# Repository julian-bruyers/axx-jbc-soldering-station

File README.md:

## Personal fork of Axel Johansson's AxxSolder
> [!NOTE]
> The purpose of this fork is not to continue the development of the offical [AxxSolder](https://github.com/AxxAxx/AxxSolder)
> but rather for some personal graphical and functional changes for my own taste. If you stumbled upon this and are interested
> in the AxxSolder project, please check out the original repository and [shop](https://www.5dimensions.se/) of Axel Johansson
> to support the project. All credits belong to him and the open-source contributers of the original project.

## AxxSolder Overview
AxxSolder is a STM32 based soldering iron controller for JBC C115, C210 and C245 style cartridges.
Two different versions are designed around the same PCB and software - one soldering station based on the [JBC ADS stand](https://www.jbctools.com/ad-sf-stand-for-t210-t245-handles-product-2018.html) and one portable version. The AxxSolder hardware takes a DC input source of 9-24V OR a USB-C Power Delivery source. The recommended power supply is a Meanwell [LRS-150-24](#recommended-power-supply) which can power all compatible JBC irons at full power. If a 65W, 20V USB-PD supply is used then NT115 and T210 handles can be powered at full power and T245 at limited power. The power limiting is automatic and AxxSolder reads the power capability of the USB-PD source during the negotiating phase and reduces the output power accordingly.
The software is written for the [STM32G431CBT6](https://www.st.com/en/microcontrollers-microprocessors/stm32g431cb.html) and implements a PID controller for temperature regulation, TFT display driver, sleep functions for when the handle is at rest and various user settings to name a few.
Enclosures for both station and portable versions are 3D printed and design files are available under [/CAD](https://github.com/AxxAxx/AxxSolder/tree/main/CAD). A video showing the AxxSolder station can be found under [DEMO](#demo). A *bill of materials* (BOM) with individual component prices can be found under [/bom](https://github.com/AxxAxx/AxxSolder/tree/main/AxxSolder_hardware/bom).

## Table of Contents
- [AxxSolder Overview](#axxsolder-overview)
- [Questions and support](#questions-and-support)
- [Features](#features)
- [DEMO](#demo)
- [Schematic](#schematic)
- [PCB](#pcb)
- [AxxSolder Station](#axxsolder-station)
- [AxxSolder Portable](#axxsolder-portable)
- [Recommended power supply for tip grounding](#recommended-power-supply-for-tip-grounding)
- [Handle identification and connections](#handle-identification-and-connections)
- [Firmware update](#firmware-update)
- [First start up after build](#first-start-up-after-build)
- [Settings](#settings)
- [PID control](#pid-control)
- [Cartridge differences](#cartridge-differences)
- [Temperature calibration](#temperature-calibration)
- [Temperature measurement](#temperature-measurement)
- [Current measurement](#current-measurement)
- [Disclaimer](#disclaimer)

## Features
- The tip temperature is set by a rotary encoder. Pressing the encoder puts AxxSolder into Sleep mode and heating is turned off, press again to wake up.
- AxxSolder is capable of driving C115, C210 and C245 style cartridges from JBC. With two handle sense inputs AxxSolder can determine if the connected handle is either a NT115, T210 or T245 and adjust max output power accordingly. The max output power is software limited to 130 W for T245, 65 W for T210 and 22 W for NT115 handles.
- When the handle is put into the stand (connected to Stand_sense) AxxSolder goes into "Standby mode". On the portable version an aluminium plate is mounted in the case and allows the AxxSolder to go into Standby mode when the cartridge or handle rests against it. After 10 min in Standby mode AxxSolder goes into "Sleep mode" and heating is completely turned off. This is similar to what JBC calls [Sleep and Hibernation](https://www.jbctools.com/intelligent-heat-management.html).
- If AxxSolder is left in normal running mode for longer than 30 min, the station automatically goes into sleep mode after 30 min as a safety feature.
- Should the temperature ever go higher than 480 deg C overheating is detected and the station goes into sleep mode in order to protect the tip.
- At start-up any USB-PD source is detected and the highest possible power is negotiated. AxxSolder limits the soldering iron output power to the max output power of the USB-PD source automatically. The maximum power output is displayed at the top of the power bar graph on the display.
- User settings are stored in non-volatile flash and can be configured via a settings menu described in [SETTINGS](#settings).
- The two buttons are used to store temperature presets, e.g. 330 deg C and 430 deg C. Both preset temperatures are configurable in the settings menu. The stored preset temperature can be updated to the current set temperature by long-pressing the preset button.
- There is a 3.3 V logic level output (GPIO4) that can be configured to go high when the iron is in Run mode, controlling e.g. fume extractor via a MosFET or relay.
- The TFT display used in this project is a 2 inch 320x240 Color TFT display [2.0" 320x240 Color IPS TFT Display](https://www.adafruit.com/product/4311) and shows information about:
  - Set temperature
  - Actual temperature
  - Current power as a bar graph
  - In case of sleep mode, the power bar shows "ZzZzZz"
  - In case of Standby mode, the power bar shows "STANDBY"
  - Input voltage
  - MCU temperature
  - Current detected handle type
  - Current max power output
  - Current power source USB-PD / DC

## Schematic
The schematic for AxxSolder is shown below. Both station and portable versions use the same PCB and software. The MCU is a [STM32G431CBT6](https://www.st.com/en/microcontrollers-microprocessors/stm32g431cb.html).

## PCB
The PCBs are designed in KiCad and manufactured by [PCBWay](https://www.pcbway.com/). PCBWay has sponsored this project with PCBs and stencils. The support and quality from PCBWay is great and therefore PCBWay is the recommender PCB supplier for this project. As some components have a rather fine pitch (0,5 mm as of the LQFP-48 package of the STM32) and some packages are "no lead" with a bottom thermal pad e.g. the WSON-8 package of the OPA2387 it is recommended to use a stencil to apply solder paste and then reflow the board using either a reflow oven or hot-plate. The boards on the image below were reflowed on a hot-plate (a homemade AxxPlate). A microscope is also recommended and helpful during assembly.
Printed Circuit Boards with assembled components are shown in the image below.

A 3D view (from and back) of the AxxSolder PCB is generated with KiCad and shown below.

## AxxSolder Station
The preferred setup is to pair AxxSolder with the [JBC ADS stand](https://www.jbctools.com/ad-sf-stand-for-t210-t245-handles-product-2018.html). This makes a very nice, compact and powerful soldering station. The JBC ADS stand is paired with a custom 3D printed enclosure for AxxSolder and the PCB is mounted with two mounting brackets. All 3D printed parts are available under [/CAD](https://github.com/AxxAxx/AxxSolder/tree/main/CAD).

The JBC ADS stand comes with a silicone cable fitted with two Binder 99-0621-00-07 connectors. In order to use this cable a Binder 99-0624-00-07 is mounted into the AxxSolder enclosure and wired as the image below:

By default, the stand separates the two signals coming from the "tool rest position" and the "tip change position" and does NOT have two separate connections for tip sensing 1 and 2 as is needed if NT115, T210 and T245 handles should all be automatically detected. Therefore, a modification is done to the PCB inside the JBC ADS stand in order to combine the "tool rest position" and the "tip change position" sense into one connection and separate the two tip sense connections. This is shown in the image above. The stand is held together with two PH0 screws from the side.
NOTE: This modification of the stand is only needed if you want to be able to use NT115, T210 and T245 with your JBC ADS stand. If you know that you will only be using T210 and/or T245 you can change the user setting: Detect NT115 to "NO" in the settings in order for T210 and T245 to be automatically detected with a un-modified JBC ADS stand.

The JBC ADS stand is an expensive piece and thankfully there are many alternatives online for the one who wants to save some money. The community on the AxxSolder Discord channel has created many enclosures for alternative stands such as the GEEBOON SDC02, and some of the AiXun stands. Some of the models are availible under [Alternative stands](https://github.com/AxxAxx/AxxSolder/tree/main/CAD/Alternative_enclosures_and_designs) .

## AxxSolder Portable
It is often nice to have a compact and portable soldering iron controller for when you are away from your comfortable desk. A neat powerful package with the same capabilities as your main soldering station. This is why AxxSolder Portable was designed. The only difference between AxxSolder station and Portable is the enclosure.
As AxxSolder accepts an input of 9-24 V it is compatible with a range of battery options. The author usually use a battery pack consisting of 12 Samsung INR18650 35E in a 3S4P configuration which works very well.
The portable version has an aluminium tab on the enclosure connected to the same input on the PCB as the "handle rest" on the station version. This allows the user to rest the iron onto the aluminium tab and automatically enter sleep mode.

The connections from the handle to the PCB through the Hirose RPC1-12RB-6P(71) connector is shown below. The Stand_sense in the portable version is connected to the aluminium plate which tells the AxxSolder to go into sleep mode when in contact with the soldering iron.

## Recommended power supply for tip grounding
In order to be able to ground the tip of the soldering iron the user MUST use a power supply with a floating output (SELV) and connect protective earth to the ground terminal on AxxSolder. No other devices should share this DC power other than AxxSolder itself. A well-suited power supply with floating output (SELV) is the Meanwell LRS-150-24. It is rated for 156 W at 24 V. By using this kind of power supply, AxxSolder can be connected directly its DC output and to mains earth thus keeping the tip of the soldering iron at earth ground potential. There is a 1A fuse after the earth terminal in paralell with a 1M resistor on the AxxSolder.
A printable cover protecting the terminals of the for LRS-150-24 can be found under [/CAD](https://github.com/AxxAxx/AxxSolder/tree/main/CAD).

Another suitable power supply is the Meanwell XLG-150-24 which has a slightly different form factor and is fully enclosed.

## Handle identification and connections
In order for AxxSolder to know which type of handle (NT115, T210, T245) is attached specific pins inside the handle connector must be connected (bridged with a jumper wire). By default, the original JBC handle T245 has NO bridged pins while inside the connector of the original JBC T210 the pins 5 and 6 are bridged with a jumper wire. The original NT115 handle from JBC has a different connector and must be modified accordingly. All the necessary connections are shown in the image below.
When powering on AxxSolder for the first time after doing these connections inside the handle connector it is wise to attach a handle without its cartridge and ensure that AxxSolder detects and shows the correct handle type on the display.
Failing to detect the handle type may cause permanent damage to the cartridge as the temperature calibration and max allowed power will be wrong.
❗WARNING❗ It has been discovered that some JBC clones have different pins bridged by the manufacturer. For example: Some AiXun T210 handles have pin 1 and 6 bridged, instead of pin 5 and 6 as AxxSolder requires for T210 handles. It is however easy to open up the connector and do the required pin connection.

## Firmware update
Flashing or updating the firmware on the STM32 MCU can be done in two ways, by using a SWD programmer or directly via USB.

### SWD programmer
These come in a variety of models and are available from several different places online. In the below example a [STLINK-V3MINIE](https://www.st.com/en/development-tools/stlink-v3minie.html) SWD programmer is used. The MCU is programmed by the following steps:
1. Disconnect any soldering iron handles from AxxSolder during the firmware update process.
2. Download the latest AxxSolder.bin file from [Releases](https://github.com/AxxAxx/AxxSolder/releases)
3. Connect your SWD programmer to the target MCU with GND, 3.3V, (N)RST, SWCLK, SWDIO
4. If your SWD programmer *can not* supply 3.3V it is necessary to power the AxxSolder from an external supply.
5. Start your programming software. [STM32CubeProgrammer](https://www.st.com/en/development-tools/stm32cubeprog.html) is used in this example.
6. Connect to the target by selecting *ST-LINK* and click on *Connect*
7. Load the latest AxxSolder.bin downloaded in *Step 2* by clicking *Open file* and select the downloaded binary file.
8. Write the firmware to the MCU by clicking *Download*.
9. If you get the message *File download complete* everything succeeded and the SWD programmer can be disconnected and AxxSolder power cycled once and AxxSolder should boot.

### USB (DFU mode)
1. Disconnect any soldering iron handles from AxxSolder during the firmware update process.
2. Download the latest AxxSolder.bin file from [Releases](https://github.com/AxxAxx/AxxSolder/releases)
3. Connect AxxSolder via USB to a computer that runs [STM32CubeProgrammer](https://www.st.com/en/development-tools/stm32cubeprog.html).
4. Hold down the most right button while powering on AxxSolder to enter DFU mode.
5. Connect to the target by selecting *USB* and click on *Connect*
6. Load the latest AxxSolder.bin downloaded in *Step 2* by clicking *Open file* and select the downloaded binary file.
7. Write the firmware to the MCU by clicking *Download*.
8. If you get the message *File download complete* everything succeeded and the USB cable can be disconnected.
9. Power cycle once and AxxSolder should boot.

## First start up after build
The first start up after you have built your AxxSolder can be intense. Double check all solder connections under a loupe/microscope. Especially the OPA2387, LTC4440 and the STM32G431 are small packages with tight pad spacing and can have solder bridges. Do also double check the connections to the soldering iron/stand which are shown in this document under [AxxSolder Station](#axxsolder-station) and [AxxSolder Portable](#axxsolder-portable).
The first thing to do after you have double-checked everything is to follow the steps under [Firmware update](#firmware-update). It is wise to do the first programming of AxxSolder without any handle piece and with only 3.3 V, not VDD. After the programming is done you can now power up AxxSolder again via either with 3.3 V, this time you can attach your handle. This allows you to test that your handle type is detected correctly (the detected handle type NT115/T210/T245 is shown in the display). The Standby feature can also be tested by touching the stand (STAND Input).
If the handle is detected correctly, the Standby function works and the display works you proceed to test the 7.35V DC/DC. This is done by once again disconnect the handle, but this time apply current limited 9-24 V VDD. 100 mA at 24 V is enough to check that the display starts and that you can measure the 3 bus voltages; 3.3V, 7.35V and VDD. If the bus voltages look good and the display shows the main screen you are ready to apply full VDD power and attach the soldering handle.
If you are not 110% sure about your soldering/connections it is wise to be on the safe side and keep your soldering tip in a water bath in over to prevent it from over-heating in an uncontrolled manner. During the development this method was used and saved a few of those expensive JBC cartridges..

## Settings
To access the user settings the user holds down the encoder button at start-up or long-press the encoder button. A SETTINGS text is then presented and the button can be released. While in the settings there are several parameters available.
| Setting | Description  | Unit | Default |
|---------|------|----------------------|----------------------|
|Startup Temp °C|Default temperature selected after boot|deg C|330|
|Temp Offset °C|Temperature offset applied to measured temperature|deg C|0|
|Standby Temp °C|Temperature to go to after handle is set in stand|deg C|150|
|Standby Time [min]|Time for which standby temperature is held before cooling down|minutes|10|
|Sleep Time [min]|Time that the iron can be ON before cooling down (safety feature)|minutes|30|
|Buzzer Enable|Enable or Disable the buzzer|YES/NO|YES|
|Preset Temp 1 °C|Preset temperature for button 1|deg C|330|
|Preset Temp 2 °C|Preset temperature for button 2|deg C|430|
|GPIO4 ON at run|Enable 3.3V output on GPIO4 when the iron is in run mode|YES/NO|NO|
|Screen rotation|Rotate the screen|0 deg, 90 deg, 180 deg, 270 deg|0 deg|
|Limit Power [W]|Limit the output power|"0"=no user limit, "5"=5 W, "10"= 10 W, "15"= 15 W ...|0|
|I measurement|Measure the heater current|YES/NO|YES|
|Startup beep|Beep after startup|YES/NO|YES|
|Temp in celcius|Show temperatures in Celcius and not Fahrenheit|YES/NO|YES|
|Temp cal 100 °C|Actual temperature at 100 °C|deg C|100|
|Temp cal 200 °C|Actual temperature at 200 °C|deg C|200|
|Temp cal 300 °C|Actual temperature at 300 °C|deg C|300|
|Temp cal 350 °C|Actual temperature at 350 °C|deg C|350|
|Temp cal 400 °C|Actual temperature at 400 °C|deg C|400|
|Temp cal 450 °C|Actual temperature at 450 °C|deg C|450|
|Serial DEBUG|Print debug over serial|YES/NO|NO|
|Displayed temp filter|Moving average filter length|Lenght|5|
|Startup temp is previous temp|Startup temp is previous used temp|YES/NO|NO|
|3-button mode|Use 3-button mode|YES/NOF|NO|
|Beep at set temp|Beep at set temp|YES/NO|YES|
|Beep tone|Beep tone|0,1,2,3|0|
|Momentary stand|Use the stand as momentary switch to go between modes (useful on AxxSolder Portable)|YES/NO|NO|
|Show power|Current power under the bar graph is displayed in this unit|W/%|W|
|Detect NT115|Detect NT115 handles or not. Useful to turn OFF for un-modified JBC SDA stands|YES/NO|YES|
|-Load Default-|Load default parameters|N/A|N/A|
|-Save and Reboot-|Exit and Save|N/A|N/A|
|-Exit no Save-|Exit without Save|N/A|N/A|

## PID control
The thermal mass and heat convection differs between different tip designs. Therefore the PID parameters should in theory be adjusted to each different cartridge. As a matter of simplification, the PID parameters are only different between the different handle types, NT115, T210 and T245. This gives a good thermal performance in conducted tests.
```c
/* Cartridge type specific PID parameters */
#define KP_NT115        5
#define KI_NT115        2
#define KD_NT115        0.3
#define MAX_I_NT115     300

#define KP_T210         7
#define KI_T210         4
#define KD_T210         0.3
#define MAX_I_T210      300

#define KP_T245         8
#define KI_T245         2
#define KD_T245         0.5
#define MAX_I_T245      300

/* General PID parameters */
#define PID_MAX_OUTPUT          500
#define PID_UPDATE_INTERVAL     25
#define PID_ADD_I_MIN_ERROR     75
double PID_NEG_ERROR_I_MULT =   7;
double PID_NEG_ERROR_I_BIAS =   1;

/* Max allowed power per handle type */
#define NT115_MAX_POWER         22
#define T210_MAX_POWER 	        65
#define T245_MAX_POWER 	        130
```
The PID parameters are adjusted to achieve a fast response with minimum overshoot and oscillation. The below image is showing the set temperature, actual temperature response as well as the P, I and D contributions during a heat-up cycle from 25 deg C to 330 deg C. This heat-up sequence takes ~1.5 seconds for a C210-007 cartridge.

## Cartridge differences
Cartridges from JBC do all contain a thermocouple element to read the tip temperature and a resistive heater element. The configuration of thermocouple and heater element differ slightly between cartridge models. In order to determine the internal configuration of the cartridges two cross sections were done. These show clearly how the C210 and C245 cartridges are constructed internally. The images can be seen here: [https://www.eevblog.com/forum/projects/axxsolder-jbc-soldering-controller](https://www.eevblog.com/forum/projects/axxsolder-jbc-soldering-controller/msg5124267/#msg5124267).
As the thermocouple output also differs (see my measurements [Temperature calibration](#temperature-calibration)) the correct handle/cartridge type has to be set. This is done automatically be the inputs "Handle_sense_1" and "Handle_sense_2" This can be done thanks to the design of the handle connector. For the JCB T210 handle pin 5 and 6 are connected internally in the connector and for NT115 pin 3 and 5 should be connected. This allows AxxSolder to sense which handle is connected and assign correct thermocouple correction, PID parameters and max output power.

## Temperature calibration
The voltage from the thermocouple embedded inside the cartridge is amplified by an OPA2387 operational amplifier and then read by the ADC of the MCU. To correlate the measured ADC value to the cartridge temperature experiments were done. A constant power was applied to the heating element of the cartridge and the ADC value was read as well as the actual tip temperature. The tip temperature was measured by a "Soldering Tip Thermocouple" used in e.g. the Hakko FG-100.
The measured data was recorded and plotted for both the C115, C210 and C245 cartridges. The specific cartridges used were the C115112, C210-007 and C245-945. The measured data were fitted to polynomial equations:
$Temp_{C115}[deg] =  5.10e^{-5} * ADC^2 + 0.42* ADC + 20.15$
$Temp_{C210}[deg] =  4.22e^{-6} * ADC^2 + 0.32* ADC + 20.97$
$Temp_{C245}[deg] = -4.73e^{-7} * ADC^2 + 0.12* ADC + 23.78$
These are then used in the software to retrieve correct tip temperatures.

The user can adjust the temperature calibration at 6 points in order to compensate for variations in the cartridge thermocouple.
To calibrate temperature(s):
- Make sure that the temperature calibration values are at their default nominal values in the settings.
- Set AxxSolder to the temperature that you want to calibrate. for example 300 deg C.
- When AxxSolder stabilizes around the setpoint, measure the actual tip temperature by using a soldering tip thermocouple, for example the HAKKO FG-100B.
- Input the actual measured temperature, let's say 302 deg C into the 300 deg C calibration setting ("Temp cal 300" = 302).

AxxSolder will then use this calibration point and correct the temperature accordingly. It will do so linearly between all calibration points.

## Temperature measurement
As the thermocouple and heater element is connected in series inside the JBC cartridges and the thermocouple voltage measures over the same pins as the heating element we have to be careful when to do the temperature measurement. In order to not disturb the thermocouple measurement with heater element switching, the switching is turned off for 0.5 ms just before the temperature measurement is taken. The 0.5 ms delay ensures that the switching is turned off and the thermocouple signal is stabilized around a stable voltage.
The measured signal over the thermocouple is clamped to 3.3V with a BAV199 Schottky diode in order to protect the op-amp OPA2387. The voltage measurement is taken by the internal ADC in DMA mode with a circular buffer. The buffer holds several measurements which are averaged and filtered in software.
The yellow curve in the image below (Channel 1) shows the PWM signal driving the gate of the MOSFET.
The green curve shows the amplified voltage between GREEN and RED wire in the JBC handle for at 330 degree C and 5% power and the purple 25 degree C and at 80% power (the tip held under water trying to heat up).
The blue pulse indicates the wait time of 0.5 ms and the purple pulse is where the ADC is sampled.

## Current measurement
The current is sampled four times per second by a 30 us current pulse through the heater. This is done both to check if there is a functioning tip in the handle (otherwise the display shows "---" at current temp) and to be able to calculate the power drawn by the heater. By knowing how much the heater draws in ampere the actual power can be calculated by knowing the bus voltage and pulse duty cycle. to measure the current the gate to the MOSFET is turned on, 10 us later the voltage over the current shunt is sampled by the ADC and the result is converted. This is shown the image below.

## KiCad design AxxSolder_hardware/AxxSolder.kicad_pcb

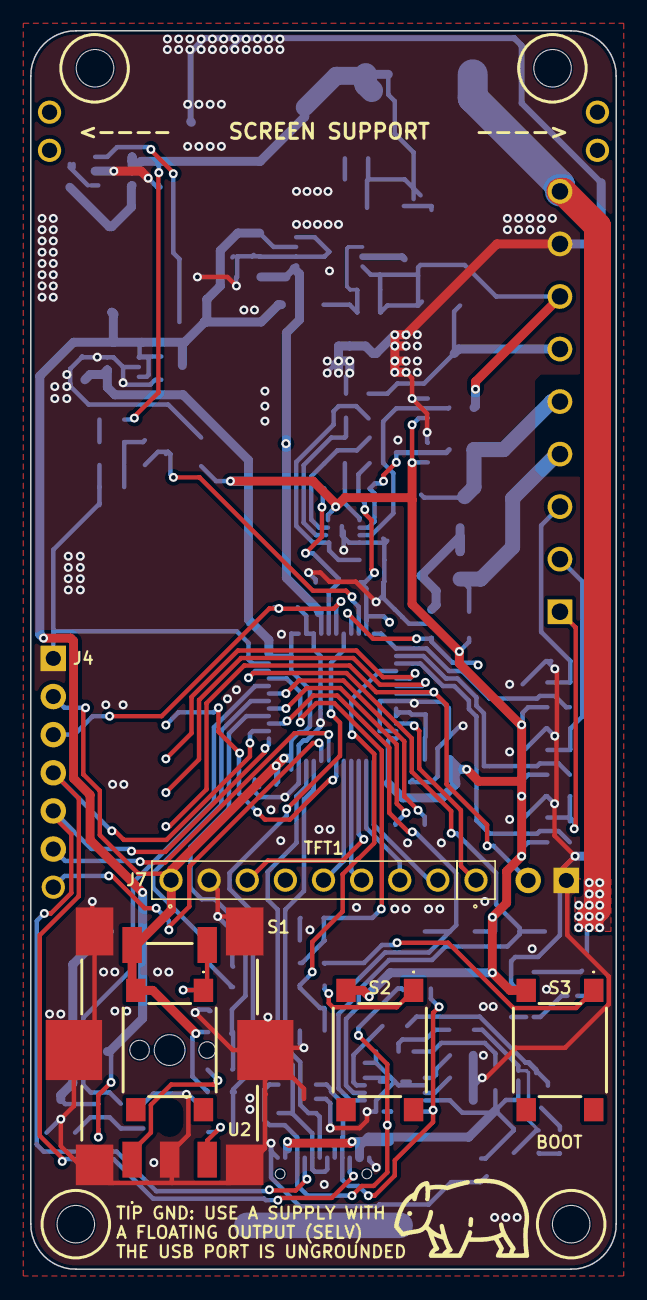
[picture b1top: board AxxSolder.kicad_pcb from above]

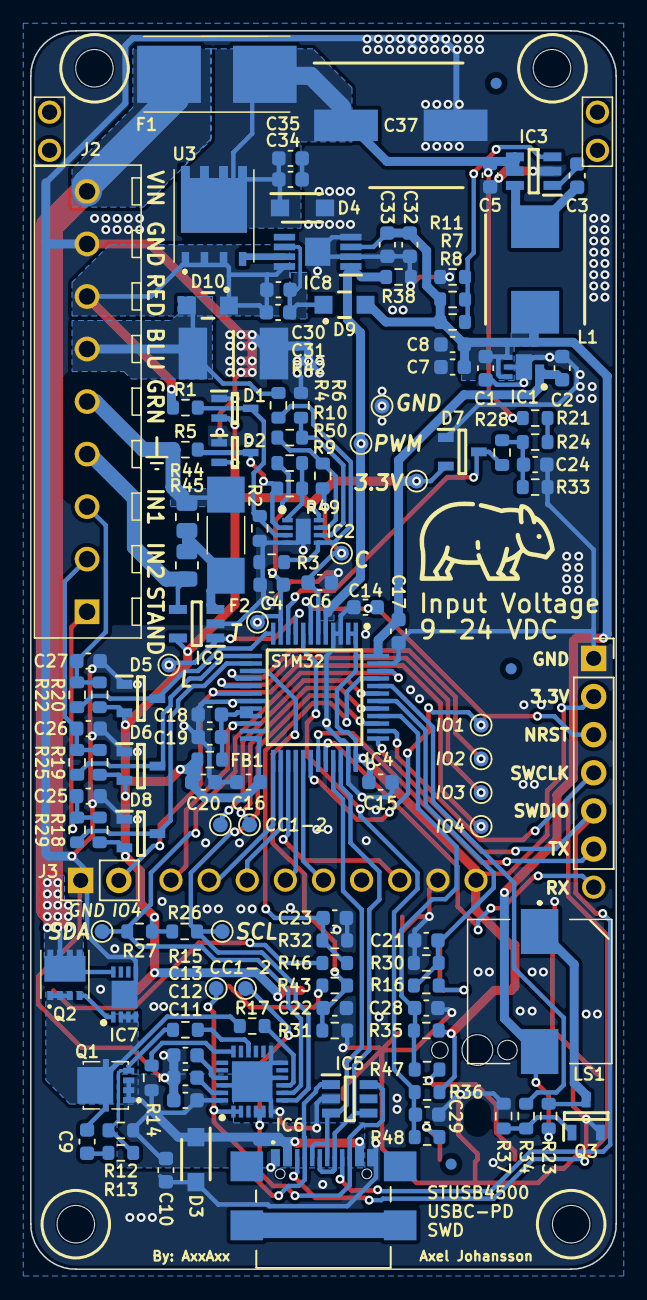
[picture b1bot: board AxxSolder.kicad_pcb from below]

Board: 2 copper layers, 39.0 x 82.5 mm, 148 parts (134 on the bottom side), 81 nets.

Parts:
C1, C2, C5, C7, C8, C10, C11, C12, C13, C19, C20, C30, C31, C32, C34, C35: 10u; C_0603_1608Metric
C3, C9, C14, C15, C16, C17, C18, C21, C22, C23, C24, C25, C26, C27, C28, C29, C33: 100n; C_0603_1608Metric
C4, C6: 1n; C_0603_1608Metric
C37: 220u; CAPAE830X1050N
D1, D2: BAV199WQ-7; SOT65P210X110-3N
D3, D4: SMF4L24AT1G; SODFL3619X98N
D5, D6, D7, D8: BAT54S; SOT95P230X110-3N
D9, D10: PMEG6020ER; PMEG6020ER115
F1: 0154007.DR; 0154100DR
F2: SF-2410FP100W-2; SF2410FP100W2
FB1: BLM18HE601SN1D; R_0603_1608Metric
FID1, FID2, FID3: Fiducial; Fiducial_0.75mm_Mask1.5mm
H1, H2: MountingHole; MountingHole_2.5mm
IC1: TLV76733DRVR; SON65P200X200X80-7N
IC2: OPA2387DSGT; SON50P200X200X80-9N
IC3: LMR54406DBVR; SOT95P280X145-6N
IC4: STM32G431CBT6; QFP50P900X900X160-48N
IC5: TPD4E1U06DBVR; SOT95P280X145-6N
IC6: STUSB4500QTR; QFN50P400X400X100-25N-D
IC7: MAX16171ATA_VY+T; SON50P300X200X80-9N
IC8: LTC4440AHMS8E; SOP65P490X110-9N
IC9: INA281A5QDBVRQ1; SOT95P280X145-5N
J1: USB4110-GF-A; USB4110GFA
J2: 691243110009
J3: TSW-102-07-T-S; PinHeader_1x02_P2.54mm_Vertical
J4: 61300611821; RHDR6W97P0X254_1X6_1574X250X865P
J5, J6: TSW-102-07-T-S; TSW-102-XX-YY-S
J7: TSW-108-07-T-S; TSW-108-XX-YY-S
L1: SRP7028CC-150M; INDPM7366X300N
LS1: CMI-9653S-SMT-TR; CMI9653SSMTTR
Q1: STL9P3LLH6
Q2: STL10N3LLH5
Q3: 2N7002NXAKR; SOT95P230X110-3N
R1, R5, R14, R17: 1k5; R_0603_1608Metric
R2, R7, R8, R9: 360k; R_0603_1608Metric
R3, R10: 220k; R_0603_1608Metric
R4, R6, R18, R19, R20, R22, R23, R25, R26, R27, R28, R29, R30, R31, R32, R33, R35, R36, R37, R38: 4k7; R_0603_1608Metric
R11, R12, R15, R21, R24: 22k; R_0603_1608Metric
R13, R16, R34, R43, R46, R47, R48: 100; R_0603_1608Metric
R42: 5m; RESC6432X89N
R44: 1M; R_0805_2012Metric
R45: 100m; R_0805_2012Metric
R49, R50: 10; R_0603_1608Metric
S1, S2, S3: ADTSM644RVTR
TFT1: Adafruit_240x320_TFT
TP1, TP2, TP4, TP5, TP6, TP7, TP8, TP14, TP15, TP16: DIAG_TP; TestPoint_Pad_D1.0mm
TP3: 3.3V_TP; TestPoint_Pad_D1.0mm
TP9, TP10: Current_TP; TestPoint_Pad_D1.0mm
TP11: TC_TP; TestPoint_Pad_D1.0mm
TP12: GND_TP; TestPoint_Pad_D1.0mm
TP13, TP18: DIAG_TP; TSW-101-XX-YY-S
TP17: SW_TP; TestPoint_Pad_D1.0mm
U2: PEC11J-9215F-S0015; PEC11J9215FS0015
U3: BSC014N04LS
wombat_logo_back***: wombat_logo_back
wombat_logo_front***: wombat_logo_front

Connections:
+3.3V: C2.1, C15.1, C16.1, C17.1, C20.2, D1.2, D2.2, D5.2 (K), D6.2 (K), D7.2 (K), D8.2 (K), FB1.2, IC1.1 (OUT), IC1.2 (SNS), IC2.8 (V+), IC4.1 (VBAT), IC4.2 (PC13), IC4.24 (VDD_1), IC4.36 (VDD_2), IC4.48 (VDD_3), IC9.5 (VS), J4.2, J7.1, R18.1, R19.1, R20.1, R26.2, R27.2, R35.2, R36.1, S1.2, S2.2, S3.2, TP3.1, U2.D1
+7.5V: C1.1, C7.2, C8.2, C32.1, C33.1, D9.2, IC1.4 (EN), IC1.6 (IN), IC8.3 (VCC), L1.2, LS1.2 (+), R7.2, R8.2, R23.1
/BLUE: D10.2, J2.6, R4.1, R42.1
/BOOST: C30.2, C31.2, D9.1, IC8.6 (BOOST)
/Buzzer: IC4.44 (PB7), R34.1
/CC1: IC5.1 (IO1), IC6.1 (CC1DB), IC6.2 (CC1), J1.A5 (CC1), TP7.1
/CC1_: IC4.43 (PB6), TP1.1
/CC2: IC5.6 (IO4), IC6.4 (CC2), IC6.5 (CC2DB), J1.B5 (CC2), TP8.1
/CC2_: IC4.41 (PB4), TP2.1
/CURRENT: C6.1, IC4.6 (PF1_-_OSC_OUT), R49.1, TP10.1
/ENC_A: C29.1, IC4.8 (PA0), R36.2, R48.1
/ENC_B: C28.1, IC4.40 (PB3), R35.1, R47.1
/GREEN: F2.2, J2.5, R5.1, R44.2
/H_sense1: C27.1, J2.3, R20.2, R22.2
/H_sense2: C26.1, J2.2, R19.2, R25.2
/Handle_inp1: D5.3 (common), IC4.12 (PA4), R22.1
/Handle_inp2: D6.3 (common), IC4.13 (PA5), R25.1
/Heater: IC4.5 (PF0_-_OSC_IN), IC8.1 (INP), R38.1, TP17.1
/I_LEAK: IC4.9 (PA1), IC9.1 (OUT), TP9.1
/NRST: C14.2, IC4.7 (PG10_-_NRST), J4.3
/RED: C30.1, C31.1, D10.1, IC8.8 (TS), J2.7, R1.1, U3.1 (S)
/S1: R16.2, S1.1, U2.E1
/SCL: IC4.39 (PA15), IC6.7 (SCL), R26.1, TP15.1
/SDA: IC4.46 (PB9), IC6.8 (SDA), R27.1, TP16.1
/SD_CS: IC4.22 (PB10), TP18.1
/SPI_CS: IC4.28 (PB14), J7.6
/SPI_DC: IC4.25 (PB11), J7.8
/SPI_MOSI: IC4.29 (PB15), J7.5
/SPI_RST: IC4.26 (PB12), J7.7
/SPI_SCK: IC4.27 (PB13), J7.3
/SW1: C21.1, IC4.42 (PB5), R16.1, R30.1
/SW2: C22.1, IC4.15 (PA7), R31.1, R43.1
/SW3: C23.1, IC4.45 (PB8-BOOT0), R32.1, R46.1
/SWCLK: IC4.38 (PA14), J1.B8 (SBU2), J4.4
/SWDIO: IC4.37 (PA13), J1.A8 (SBU1), J4.5
/S_sense: C25.1, J2.1, R18.2, R29.2
/Stand_inp: D8.3 (common), IC4.14 (PA6), R29.1
/TC: C4.1, IC4.11 (PA3), R50.1, TP11.1
/USART_RX: IC4.32 (PA10), TP13.1
/USART_TX: IC4.31 (PA9), J4.6
/USB_D+: IC4.34 (PA12), IC5.4 (IO3), J1.A6 (D+), J1.B6 (D+)
/USB_D-: IC4.33 (PA11), IC5.3 (IO2), J1.A7 (D-), J1.B7 (D-)
/USR1: IC4.30 (PA8), TP4.1
/USR2: IC4.16 (PB0), TP6.1
/USR3: IC4.17 (PB1), TP5.1
/USR4: IC4.18 (PB2), J3.2, TP14.1
/VBUS: C10.2, C11.1, D3.1 (K), IC6.24 (VDD), J1.A4 (VBUS), J1.A9 (VBUS), J1.B4 (VBUS), J1.B9 (VBUS), Q1.1 (S), R12.2, R14.2
/VBUS_IN: D7.3 (common), IC4.10 (PA2), R28.2
/VCCA: C18.1, C19.1, FB1.1, IC4.20 (VREF+), IC4.21 (VDDA)
/VDD_IN: F1.2, IC7.8 (OUT), J2.9, Q2.5 (D)
/VDD_IN_USBCPD: C9.2, IC7.2 (SRC), IC7.3 (IN), IC7.4 (EN), Q1.5 (D), Q2.1 (S), R17.2
Earth: IC9.4 (IN-), J2.4, R45.1
GND: C1.2, C2.2, C4.2, C5.1, C6.2, C7.1, C8.1, C10.1, C11.2, C12.2, C13.2, C14.1, C15.2, C16.2, C17.2, C18.2, C19.2, C20.1, C21.2, C22.2, C23.2, C24.2, C25.2, C26.2, C27.2, C28.2, C29.2, C32.2, C33.2, C34.1, C35.1, C37.2, D1.1, D2.1, D3.2 (A), D4.2 (A), D5.1 (A), D6.1 (A), D7.1 (A), D8.1 (A), IC1.3 (GND_1), IC1.5 (GND_2), IC1.7 (EP), IC2.4 (V-), IC2.9 (THERMAL_PAD), IC3.2 (GND), IC4.3 (PC14_-_OSC32_IN), IC4.4 (PC15_-_OSC32_OUT), IC4.19 (VSSA), IC4.23 (VSS_1), IC4.35 (VSS_2), IC4.47 (VSS_3), IC5.2 (GND), IC6.6 (RESET), IC6.10 (GND), IC6.12 (ADDR0), IC6.13 (ADDR1), IC6.22 (VSYS), IC6.25 (EP), IC7.5 (GND), IC7.9 (EP), IC8.2 (GND_1), IC8.4 (GND_2), IC8.9 (EP), IC9.2 (GND), J1.A1 (GND), J1.A12 (GND), J1.B1 (GND), J1.B12 (GND), J2.8, J3.1, J4.1, J7.2, Q3.2 (S), R2.2, R3.2, R6.2, R11.1, R30.2, R31.2, R32.2, R33.2, R37.2, R38.2, R42.2, TP12.1, U2.B1, U2.MP
unnamed: C9.1, R13.2
unnamed: C24.1, R24.1, R28.1, R33.1
unnamed: IC2.1, R9.1, R50.2
unnamed: IC2.7, R10.1, R49.2
unnamed: D1.3, IC2.3 (+), R1.2, R2.1
unnamed: D2.3, IC2.2 (-), R5.2, R9.2
unnamed: IC2.5 (+), R3.1, R4.2
unnamed: IC2.6 (-), R6.1, R10.2
unnamed: C3.1, IC3.1 (CB)
unnamed: IC3.3 (FB), R7.1, R8.1, R11.2
unnamed: C3.2, IC3.6 (SW), L1.1
unnamed: IC6.9 (DISCH), R17.1
unnamed: IC6.16 (VBUS_EN_SNK), R15.1
unnamed: IC6.18 (VBUS_VS_DISCH), R14.1
unnamed: C13.1, IC6.21 (VREG_1V2)
unnamed: C12.1, IC6.23 (VREG_2V7)
unnamed: IC7.1 (GATE), Q2.4 (G)
unnamed: IC8.7 (TG), U3.9 (G)
unnamed: F2.1, IC9.3 (IN+), R44.1, R45.2
unnamed: LS1.1 (-), Q3.3 (D), R23.2
unnamed: Q1.4 (G), R12.1, R13.1, R15.2
unnamed: Q3.1 (G), R34.2, R37.1
unnamed: R21.1, R24.2
unnamed: R43.2, S2.1
unnamed: R46.2, S3.1
unnamed: R47.2, U2.A1
unnamed: R48.2, U2.C1
VDD: C5.2, C34.2, C35.2, C37.1, D4.1 (K), F1.1, IC3.4 (EN), IC3.5 (VIN), R21.2, U3.10 (D)

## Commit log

2025-10-10 repo: Remove .github folder
2025-10-10 feat: Add wombat log
2025-10-10 fix: Rename original gerber folder
2025-10-10 feat: Change logos and silscreen texts
2025-10-10 feat: Create new gerbe files
2025-10-10 docs: Update README for personal repo
